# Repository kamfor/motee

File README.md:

# motee_v3
Highly integrated actuator for robotics

### Components
* Pololu micro DC HP motor
* Magnetic encoder
* STM32  MCU
* TI high current H bridge
* RS485 controller 
* Logic Level converter 
* Current sensor

### Features
* Multi Master communication
* Easy commands
* Expansibility
* Arduino, Rbpi, AVR, ARM, PIC, PC compatibility 
* Task controlled
* High torque 
* ...

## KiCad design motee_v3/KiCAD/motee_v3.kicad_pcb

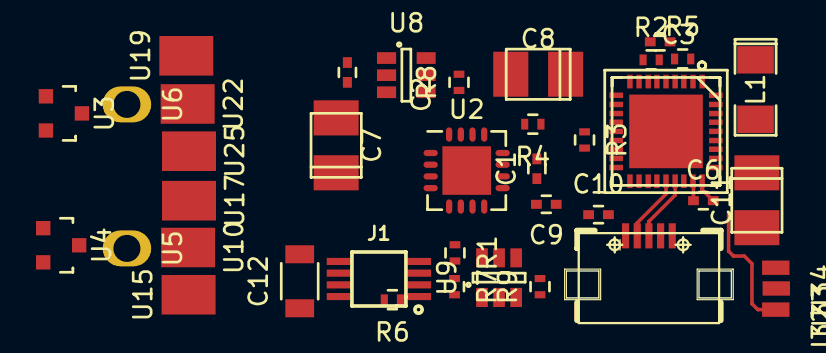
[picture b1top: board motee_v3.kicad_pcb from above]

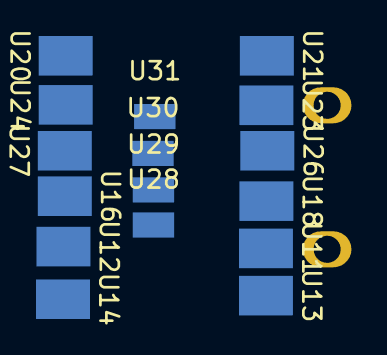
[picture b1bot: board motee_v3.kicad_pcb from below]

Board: 2 copper layers, 55 parts (16 on the bottom side), 34 nets.

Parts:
C1, C2, C3, C6, C9, C10: C_Small; C_0402
C7, C8, C11: CP1_Small; TantalC_SizeT_EIA-3528
C12: CP1_Small; C_1206
J1: SN65HVD3082EDGK; VSSOP8_P0.65mm_W3mm
L1: L_Small; SMD-1206_Pol
R1, R2, R3, R4, R5, R6, R7, R8, R9: R; R_0402
U1: STM32F103; untitled-QFN50P600X600X100-37N
U2: DRV8801; UQFN-16-1EP_4x4mm_Pitch0.65mm
U3, U4: TLE4946-2K; SOT-23
U5, U6: pad_round
U7: micro-usb; microusb-USB-MICRO-SMD
U8, U9: LP38693; SOT-23-6
U10, U11, U12, U13, U14, U15, U16, U17, U18, U19, U20, U21, U22, U23, U24, U25, U26, U27: pad; pad_square
U28, U29, U30, U31: pad; pad_zlacze
U32, U33, U34: pad; pad_isp

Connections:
+3V3: C6.2, C11.1, C12.1, J1.8, L1.1, R3.2, R4.2, R6.2, R8.2, R9.2, U1.1, U1.19, U1.27, U3.1, U4.1, U8.4, U8.5, U9.4, U9.5
+8V: C2.2, C7.1, C9.2, U2.8, U8.1, U8.6, U30.1
A: J1.6, U29.1
ADC: R2.1, U1.8, U2.14
B: J1.7, U28.1
D+: U1.24, U7.3
D-: U1.23, U7.2
DIR: J1.2, J1.3, R7.2, U1.12
GND: C3.2, C6.1, C7.2, C8.2, C9.1, C10.1, C11.2, C12.2, J1.5, R1.2, R2.2, R7.1, U1.5, U1.18, U1.26, U1.36, U2.2, U2.12, U3.3, U4.3, U7.5, U8.2, U9.2, U13.1, U14.1, U15.1, U31.1, U34.1
HALL1: U1.34, U3.2, U19.1, U20.1, U21.1
HALL2: U1.33, U4.2, U16.1, U17.1, U18.1
IN1: U1.11, U2.16
IN2: U1.10, U2.5
MCU_RXD0: J1.1, R6.1, U1.22
MCU_TXD0: J1.4, U1.21
unnamed: C1.1, U2.10
unnamed: C1.2, U2.11
unnamed: C2.1, U2.13
unnamed: C3.1, L1.2, U1.6
unnamed: R1.1, U2.7
unnamed: R5.1, U1.4
unnamed: R8.1, U8.3
unnamed: R9.1, U9.3
unnamed: U2.6, U5.1
unnamed: U2.9, U6.1
unnamed: U10.1, U11.1, U12.1
OUT1: U25.1, U26.1, U27.1
OUT2: U22.1, U23.1, U24.1
PWM: U1.20, U2.4
SWCLK: U1.28, U33.1
SWDIO: U1.25, U32.1
VBUS: C8.1, C10.2, U7.1, U9.1, U9.6
nFAULT: R4.1, U1.13, U2.15
nSLEEP: R3.1, U1.14, U2.3

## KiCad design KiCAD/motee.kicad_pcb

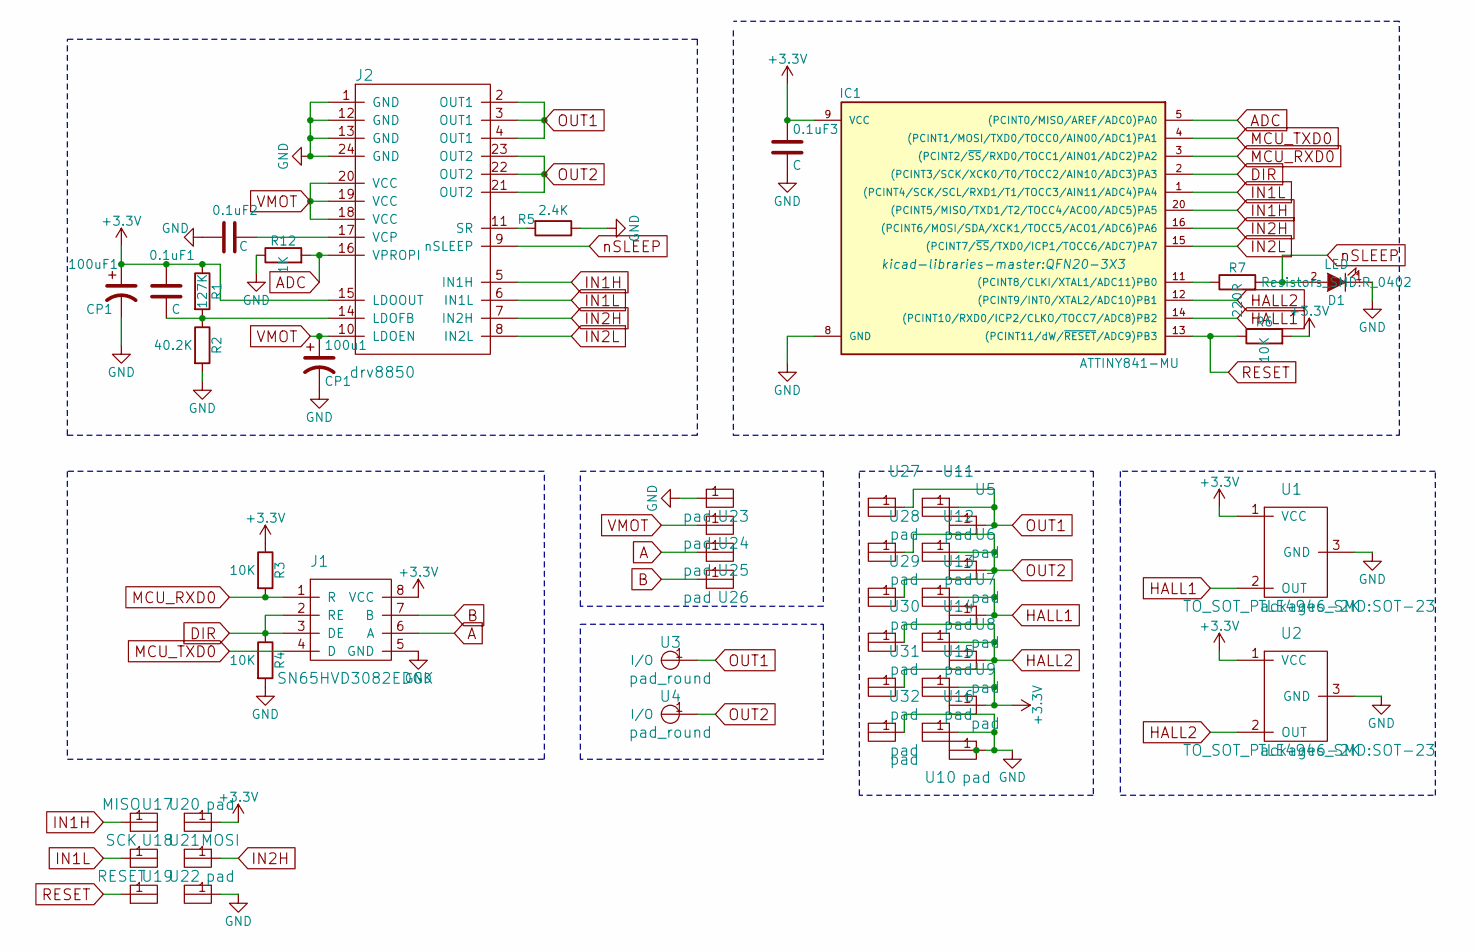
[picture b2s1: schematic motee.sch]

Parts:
0.1uF1, 0.1uF2, 0.1uF3: C; C_0603
100u1, 100uF1: CP1; TantalC_SizeB_EIA-3528_Reflow
D1: LED; R_0402
IC1: ATTINY841-MU; QFN20-3X3
J1: SN65HVD3082EDGK; VSSOP8_P0.65mm_W3mm
J2: drv8850; DRV8850_RGY_24
R1: 127K; R_0402
R2: 40.2K; R_0402
R3, R4, R6: 10K; R_0402
R5: 2.4K; R_0402
R7: 220R; R_0402
R12: 1K; R_0402
U1, U2: TLE4946-2K; SOT-23
U3, U4: pad_round
U5, U6, U7, U8, U9, U10, U27, U28, U29, U30, U31, U32: pad; square_22x22
U11, U12, U13, U14, U15, U16: pad; pad_square
U17: MISO; pad_isp
U18: SCK; pad_isp
U19: RESET; pad_isp
U20, U22: pad; pad_isp
U21: MOSI; pad_isp
U23, U24, U25, U26: pad; pad_zlacze

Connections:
+3V3: 0.1uF1.1, 0.1uF3.1, 100uF1.1, IC1.9 (VCC), J1.8 (VCC), J2.15 (LDOOUT), R1.1, R3.1, R6.2, U1.1 (VCC), U2.1 (VCC), U9.1, U15.1, U20.1, U31.1
A: J1.6 (A), U25.1
ADC: IC1.5 ((PCINT0/MISO/AREF/ADC0)PA0), J2.16 (VPROPI), R12.2
B: J1.7 (B), U26.1
DIR: IC1.2 ((PCINT3/SCK/XCK0/T0/TOCC2/AIN10/ADC3)PA3), J1.2 (RE), J1.3 (DE), R4.1
GND: 0.1uF2.2, 0.1uF3.2, 100u1.2, 100uF1.2, D1.1 (K), IC1.8 (GND), J1.5 (GND), J2.1 (GND), J2.12 (GND), J2.13 (GND), J2.24 (GND), R2.2, R4.2, R5.1, R12.1, U1.3 (GND), U2.3 (GND), U10.1, U16.1, U22.1, U23.1, U32.1
HALL1: IC1.14 ((PCINT10/RXD0/ICP2/CLKO/TOCC7/ADC8)PB2), U1.2 (OUT), U7.1, U13.1, U29.1
HALL2: IC1.12 ((PCINT9/INT0/XTAL2/ADC10)PB1), U2.2 (OUT), U8.1, U14.1, U30.1
IN1H: IC1.20 ((PCINT5/MISO/TXD1/T2/TOCC4/ACO0/ADC5)PA5), J2.5 (IN1H), U17.1
IN1L: IC1.1 ((PCINT4/SCK/SCL/RXD1/T1/TOCC3/AIN11/ADC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), J2.6 (IN1L), U18.1
IN2H: IC1.16 ((PCINT6/MOSI/SDA/XCK1/TOCC5/ACO1/ADC6)P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), J2.7 (IN2H), U21.1
IN2L: IC1.15 ((PCINT7/~SS~/TXD0/ICP1/TOCC6/ADC7)PA7), J2.8 (IN2L)
MCU_RXD0: IC1.3 ((PCINT2/~SS~/RXD0/TOCC1/AIN01/ADC2)PA2), J1.1 (R), R3.2
MCU_TXD0: IC1.4 ((PCINT1/MOSI/TXD0/TOCC0/AIN00/ADC1)PA1), J1.4 (D)
unnamed: 0.1uF1.2, J2.14 (LDOFB), R1.2, R2.1
unnamed: 0.1uF2.1, J2.17 (VCP)
unnamed: IC1.11 ((PCINT8/CLKI/XTAL1/ADC11)PB0), R7.1
unnamed: J2.11 (SR), R5.2
OUT1: J2.2 (OUT1), J2.3 (OUT1), J2.4 (OUT1), U3.1, U5.1, U11.1, U27.1
OUT2: J2.21 (OUT2), J2.22 (OUT2), J2.23 (OUT2), U4.1, U6.1, U12.1, U28.1
RESET: IC1.13 ((PCINT11/dW/~RESET~/ADC9)PB3), R6.1, U19.1
VMOT: 100u1.1, J2.10 (LDOEN), J2.18 (VCC), J2.19 (VCC), J2.20 (VCC), U24.1
nSLEEP: D1.2 (A), J2.9 (nSLEEP), R7.2

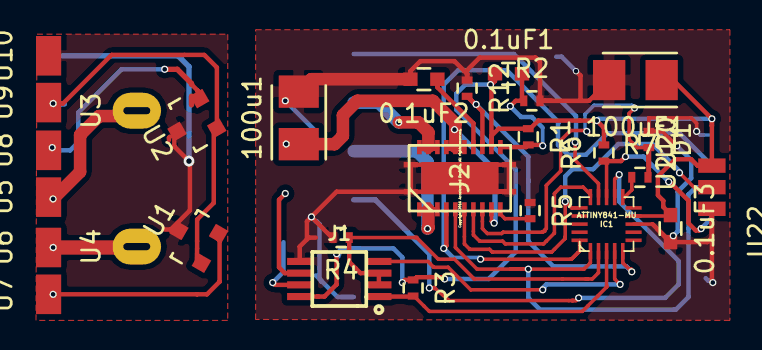
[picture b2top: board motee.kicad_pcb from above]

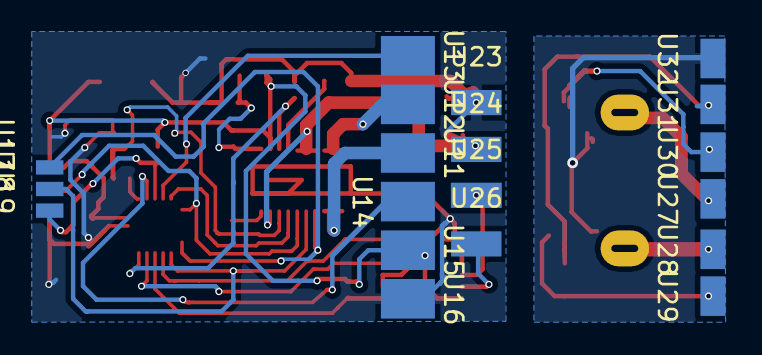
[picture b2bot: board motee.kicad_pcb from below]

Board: 2 copper layers, 49 parts (19 on the bottom side), 23 nets.

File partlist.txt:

Electronic components table 
+--------------------+-------------+-------------+---------+-----------------------------------------------------------------------------------------------------+
| Name               | Package     |  Area       | Price   | Link                                                                                                |
+--------------------+-------------+-------------+---------+-----------------------------------------------------------------------------------------------------+
| DRV8850RGYR        | VQFN-24     |  20,6225mm2 | 4,3zł   | http://pl.farnell.com/texas-instruments/drv8850rgyr/motor-dr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        |
+--------------------+-------------+-------------+---------+-----------------------------------------------------------------------------------------------------+
| ATTINY841-MU       | QFN-20      |  16,0000mm2 | 5,18zł  | http://pl.farnell.com/atmel/attiny841-mu/mcu-attiny-8kb-16mh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                     |
+--------------------+-------------+-------------+---------+-----------------------------------------------------------------------------------------------------+
| SN65HVD3082EDGK    | VSSOP-8     |  31,0000mm2 | 10,5zł  | http://pl.farnell.com/texas-instruments/sn65hvd3082edgk/tran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  |
+--------------------+-------------+-------------+---------+-----------------------------------------------------------------------------------------------------+
| TLE4946-2K 2pcs    | SC-59       |  16,8000mm2 | 7,00zł  | http://pl.farnell.com/infineon/tle4946-2k/hall-effect-sensor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                 |
+--------------------+-------------+-------------+---------+-----------------------------------------------------------------------------------------------------+
| Passives(approx)   | SMD         |  100,000mm2 | 15,5zł  | Including cables and connectors                                                                     |
+--------------------+-------------+-------------+---------+-----------------------------------------------------------------------------------------------------+
                                          Total: | 42,48zł |
                                                 +---------+
Mechanics
+--------------------+-------------+-------------+---------+-----------------------------------------------------------------------------------------------------+
| Name               | Package     |  Area       | Price   | Link                                                                                                |
+--------------------+-------------+-------------+---------+-----------------------------------------------------------------------------------------------------+
| 30:1 HPCBdualshaft | ND          |  ND         | 75,15zł | https://www.pololu.com/product/3072                                                                 |
+--------------------+-------------+-------------+---------+-----------------------------------------------------------------------------------------------------+
| PCB 1 25x15mm      | ND          |  ND         | 11,25zł | http://prototypy.com/sites_pcbplugins/pcborder/58                                                   |
+--------------------+-------------+-------------+---------+-----------------------------------------------------------------------------------------------------+
| PCB 2 15X15mm      | ND          |  ND         | 2,58zł  | http://prototypy.com/sites_pcbplugins/pcborder/58                                                   |
+--------------------+-------------+-------------+---------+-----------------------------------------------------------------------------------------------------+
| Enc. Disc magn.    | ND          |  ND         | 2,75zł  | https://www.pololu.com/product/2599                                                                 |
+--------------------+-------------+-------------+---------+-----------------------------------------------------------------------------------------------------+
                                          Total: | 91,73zł |
                                                 +---------+
                                        Summary: | 134,21zł|
                                                 +---------+

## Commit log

2016-02-11 Update README.md
    Few minor changes
2016-02-16 initial commit.
2016-02-16 First sketch of schematic.
2016-02-16 Minor fixes in schematic.
2016-02-17 Encoder has been added.
2016-04-01 test
2016-04-02 blas
2016-04-02 initial
2016-04-20 poprawki
2016-04-30 poprawiona
2016-05-08 gerbery
2016-05-09 gerbery_v2
2016-05-14 makefile
2016-09-11 ver3
2016-09-13 dodane wartosci elementow
2016-09-14 rezystor i dioda 0805
2016-09-29 wylane masy i boot0
2017-01-22 bug fixes
2017-10-23 blinky v3.1
2017-10-26 krzaki hardwarowe
2017-10-29 ADC_current
2017-11-02 encoder works
2017-11-07 simple PID
2017-11-14 hardware bug
2017-11-30 gui layouts
2017-12-10 gui devlist
2017-12-16 usart frame handling
2018-01-07 data plot from nucleo
2018-01-07 motee communication protocol
2018-01-08 rs485 tests
2018-01-10 battery suport
2018-01-15 rs485 works
2018-01-16 pid loop fail
2018-01-19 usb config
2018-01-20 Pid Works
2018-01-21 USB ready to grade
2018-01-21 rs work
2018-01-22 code refactor
2018-06-17 aktualizacja

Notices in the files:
parts and their libraries:
Copyright 2016 Accelerated Designs. All rights reserved.
